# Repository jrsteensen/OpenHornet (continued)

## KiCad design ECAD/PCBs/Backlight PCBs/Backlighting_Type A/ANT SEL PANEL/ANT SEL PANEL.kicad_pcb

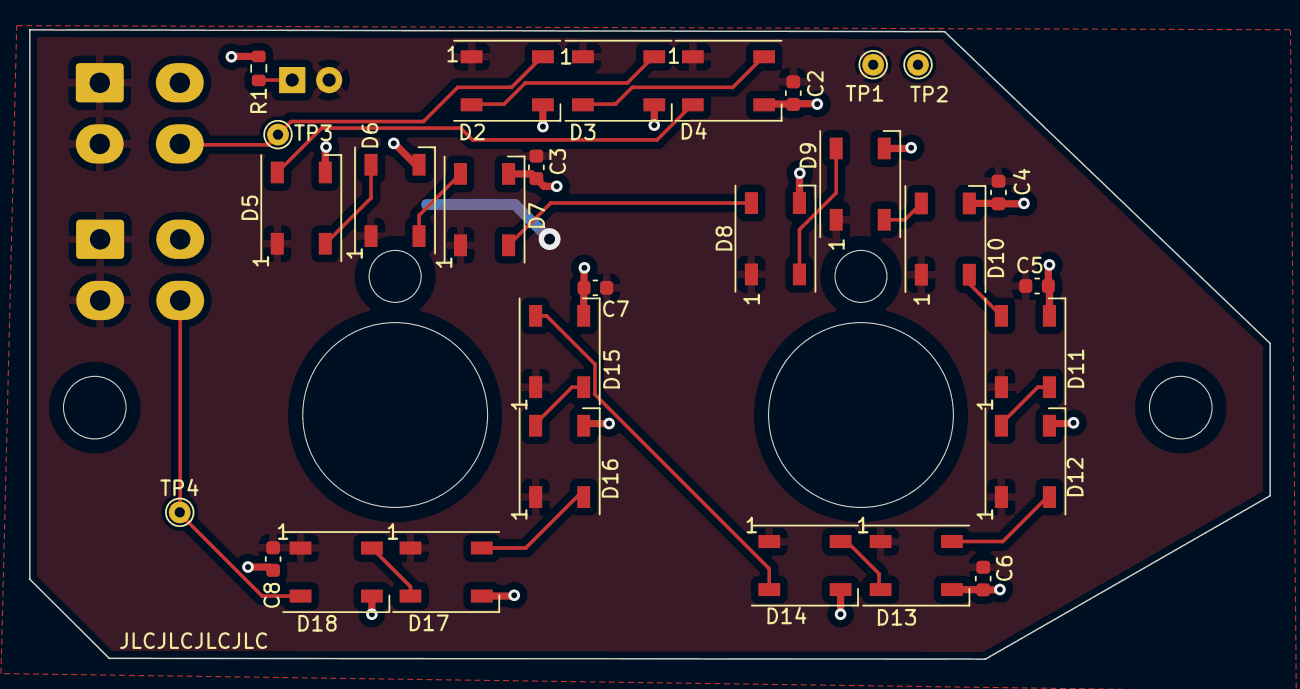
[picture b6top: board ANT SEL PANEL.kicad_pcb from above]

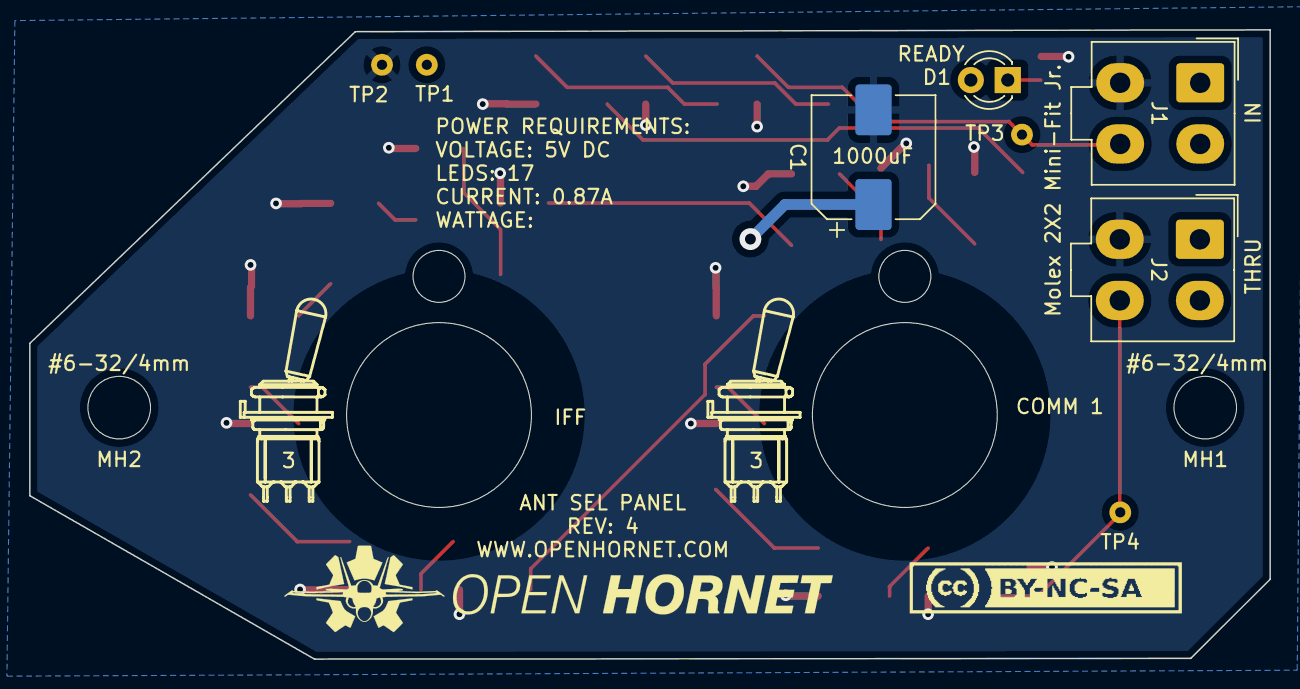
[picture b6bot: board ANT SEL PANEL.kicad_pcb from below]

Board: 2 copper layers, 85.2 x 43.2 mm, 41 parts (10 on the bottom side), 21 nets.

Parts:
C1: 1000uF; CP_Elec_8x10
C2, C3, C4, C5, C6, C7, C8: 0.1uF; C_0603_1608Metric
D1: Green; LED_D3.0mm
D2, D3, D4, D5, D6, D7, D8, D9, D10, D11, D12, D13, D14, D15, D16, D17, D18: WS2812B; LED_WS2812B_PLCC4_5.0x5.0mm_P3.2mm
J1, J2: Mini-Fit Jr. 2x02; Molex_Mini-Fit_Jr_5566-04A_2x02_P4.20mm_Vertical
LOGO1: LOGO; LOGO_OH_Text_Small
LOGO2: LOGO; LOGO_CC-BY-NC-SA_Half_Small
MH1, MH2: 6x32 / 4mm; MountingHole_6-32_PHS
MH3, MH4: Switch_100SPx; 100SPX_Toggle_13mm_x_18mm
R1: 470; R_0603_1608Metric
Ref**: 100SP3 Toggle; 100SP3_Toggle_Silkscreen
Ref**#2: 100SP3 Toggle; 100SP3_Toggle_Silkscreen
TP1, TP2, TP3, TP4: TestPoint; TestPoint_THTPad_D1.5mm_Drill0.7mm

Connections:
+5V: C1.1, C2.1, C3.1, C4.1, C5.1, C6.1, C7.1, C8.1, D1.2 (A), D2.1 (VDD), D3.1 (VDD), D4.1 (VDD), D5.1 (VDD), D6.1 (VDD), D7.1 (VDD), D8.1 (VDD), D9.1 (VDD), D10.1 (VDD), D11.1 (VDD), D12.1 (VDD), D13.1 (VDD), D14.1 (VDD), D15.1 (VDD), D16.1 (VDD), D17.1 (VDD), D18.1 (VDD), J1.1, J1.2 (Pin_3), J2.1, J2.2 (Pin_3), TP1.1
/DATA1: D7.2 (DOUT), D8.4 (DIN)
/DATA2: D12.2 (DOUT), D13.4 (DIN)
/DATA3: D16.2 (DOUT), D17.4 (DIN)
DATA IN: D2.4 (DIN), J1.4, TP3.1
DATA OUT: D18.2 (DOUT), J2.4, TP4.1
GND: C1.2, C2.2, C3.2, C4.2, C5.2, C6.2, C7.2, C8.2, D2.3 (VSS), D3.3 (VSS), D4.3 (VSS), D5.3 (VSS), D6.3 (VSS), D7.3 (VSS), D8.3 (VSS), D9.3 (VSS), D10.3 (VSS), D11.3 (VSS), D12.3 (VSS), D13.3 (VSS), D14.3 (VSS), D15.3 (VSS), D16.3 (VSS), D17.3 (VSS), D18.3 (VSS), J1.3 (Pin_2), J2.3 (Pin_2), R1.1, TP2.1
unnamed: D1.1 (K), R1.2
unnamed: D2.2 (DOUT), D3.4 (DIN)
unnamed: D3.2 (DOUT), D4.4 (DIN)
unnamed: D4.2 (DOUT), D5.4 (DIN)
unnamed: D5.2 (DOUT), D6.4 (DIN)
unnamed: D6.2 (DOUT), D7.4 (DIN)
unnamed: D8.2 (DOUT), D9.4 (DIN)
unnamed: D9.2 (DOUT), D10.4 (DIN)
unnamed: D10.2 (DOUT), D11.4 (DIN)
unnamed: D11.2 (DOUT), D12.4 (DIN)
unnamed: D13.2 (DOUT), D14.4 (DIN)
unnamed: D14.2 (DOUT), D15.4 (DIN)
unnamed: D15.2 (DOUT), D16.4 (DIN)
unnamed: D17.2 (DOUT), D18.4 (DIN)
